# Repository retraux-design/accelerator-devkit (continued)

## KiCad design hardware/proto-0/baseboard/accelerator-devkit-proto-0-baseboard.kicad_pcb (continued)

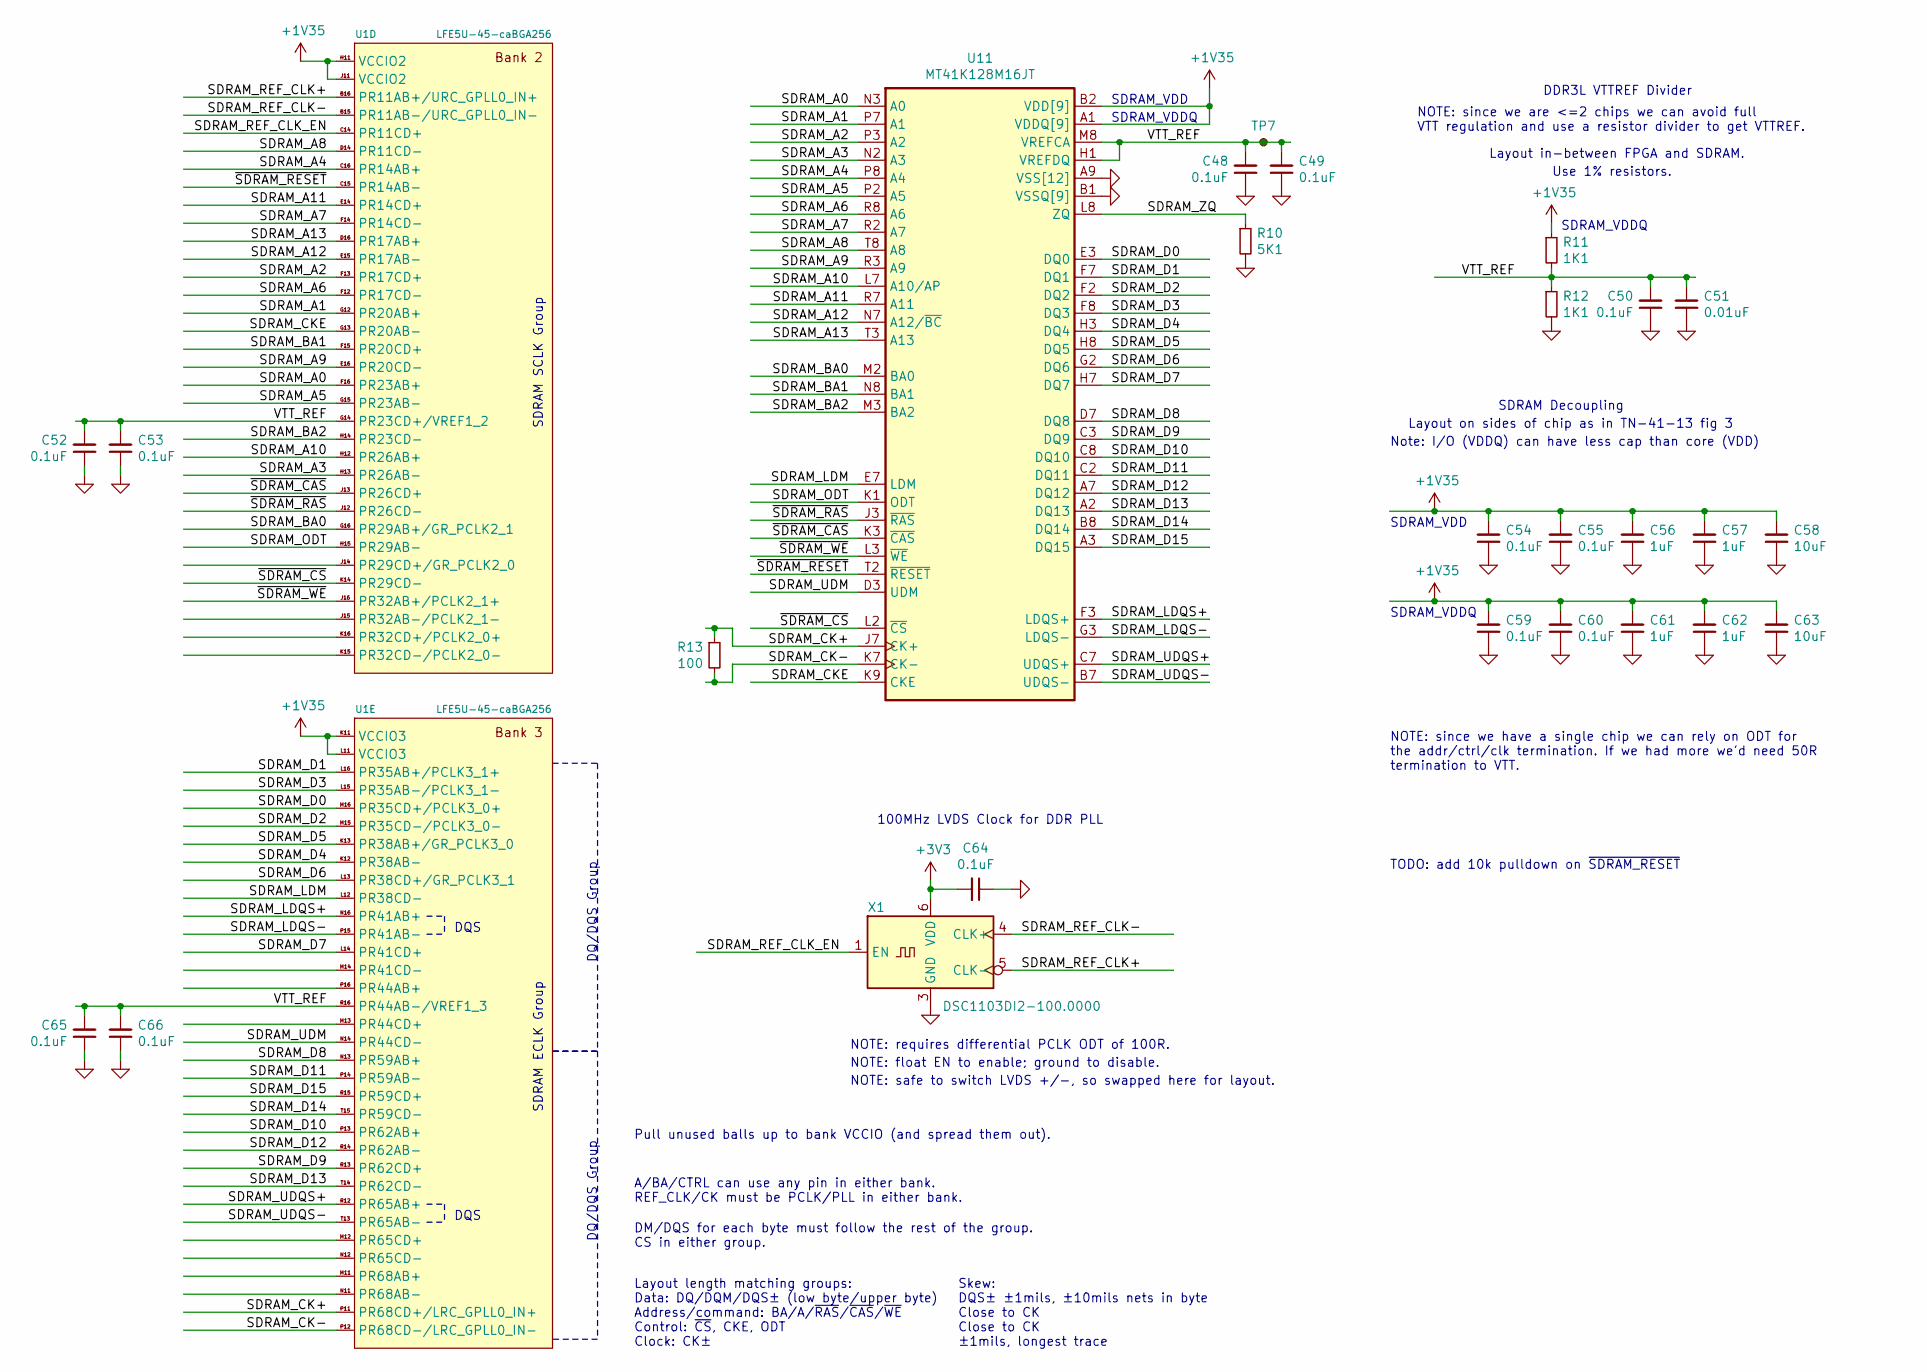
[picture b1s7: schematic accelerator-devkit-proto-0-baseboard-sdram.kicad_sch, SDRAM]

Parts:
C48, C49, C50, C52, C53, C54, C55, C59, C60, C65, C66: 0.1uF; C_0201_0603Metric
C51: 0.01uF; C_0201_0603Metric
C56, C57, C61, C62: 1uF; C_0201_0603Metric
C58, C63: 10uF; C_0402_1005Metric
C64: 0.1uF; C_0402_1005Metric
R10: 5K1; R_0402_1005Metric
R11, R12: 1K1; R_0402_1005Metric
R13: 100; R_0402_1005Metric
TP7: TestPoint_Small; TestPoint_Pad_D1.0mm
U1: LFE5U-45-caBGA256; Lattice_caBGA-256_14x14mm_P0.8mm
U11: MT41K128M16JT; BGA-96_9.0x13.0mm_Layout2x3x16_P0.8mm
X1: DSC1103DI2-100.0000; Oscillator_SMD_Microchip_VDFN-6Pin_2.5x2.0mm_J7A

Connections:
+1V35: C54.2, C55.2, C56.2, C57.2, C58.2, C59.2, C60.2, C61.2, C62.2, C63.2, R11.1, U1.H11 (VCCIO2), U1.J11 (VCCIO2), U1.K11 (VCCIO3), U1.L11 (VCCIO3), U11.A1 (VDDQ[9]), U11.A8 (VDDQ), U11.B2 (VDD[9]), U11.C1 (VDDQ), U11.C9 (VDDQ), U11.D2 (VDDQ), U11.D9 (VDD), U11.E9 (VDDQ), U11.F1 (VDDQ), U11.G7 (VDD), U11.H2 (VDDQ), U11.H9 (VDDQ), U11.K2 (VDD), U11.K8 (VDD), U11.N1 (VDD), U11.N9 (VDD), U11.R1 (VDD), U11.R9 (VDD); also elsewhere on the board
+3V3: C64.2, X1.6 (VDD); also elsewhere on the board
/SDRAM/SDRAM_A0: U1.F16 (PR23AB+), U11.N3 (A0)
/SDRAM/SDRAM_A1: U1.G12 (PR20AB+), U11.P7 (A1)
/SDRAM/SDRAM_A2: U1.F13 (PR17CD+), U11.P3 (A2)
/SDRAM/SDRAM_A3: U1.H13 (PR26AB-), U11.N2 (A3)
/SDRAM/SDRAM_A4: U1.C16 (PR14AB+), U11.P8 (A4)
/SDRAM/SDRAM_A5: U1.G15 (PR23AB-), U11.P2 (A5)
/SDRAM/SDRAM_A6: U1.F12 (PR17CD-), U11.R8 (A6)
/SDRAM/SDRAM_A7: U1.F14 (PR14CD-), U11.R2 (A7)
/SDRAM/SDRAM_A8: U1.D14 (PR11CD-), U11.T8 (A8)
/SDRAM/SDRAM_A9: U1.E16 (PR20CD-), U11.R3 (A9)
/SDRAM/SDRAM_A10: U1.H12 (PR26AB+), U11.L7 (A10/AP)
/SDRAM/SDRAM_A11: U1.E14 (PR14CD+), U11.R7 (A11)
/SDRAM/SDRAM_A12: U1.E15 (PR17AB-), U11.N7 (A12/~BC)
/SDRAM/SDRAM_A13: U1.D16 (PR17AB+), U11.T3 (A13)
/SDRAM/SDRAM_BA0: U1.G16 (PR29AB+/GR_PCLK2_1), U11.M2 (BA0)
/SDRAM/SDRAM_BA1: U1.F15 (PR20CD+), U11.N8 (BA1)
/SDRAM/SDRAM_BA2: U1.H14 (PR23CD-), U11.M3 (BA2)
/SDRAM/SDRAM_CK+: R13.1, U1.P11 (PR68CD+/LRC_GPLL0_IN+), U11.J7 (CK+)
/SDRAM/SDRAM_CK-: R13.2, U1.P12 (PR68CD-/LRC_GPLL0_IN-), U11.K7 (CK-)
/SDRAM/SDRAM_CKE: U1.G13 (PR20AB-), U11.K9 (CKE)
/SDRAM/SDRAM_D0: U1.M16 (PR35CD+/PCLK3_0+), U11.E3 (DQ0)
/SDRAM/SDRAM_D1: U1.L16 (PR35AB+/PCLK3_1+), U11.F7 (DQ1)
/SDRAM/SDRAM_D2: U1.M15 (PR35CD-/PCLK3_0-), U11.F2 (DQ2)
/SDRAM/SDRAM_D3: U1.L15 (PR35AB-/PCLK3_1-), U11.F8 (DQ3)
/SDRAM/SDRAM_D4: U1.K12 (PR38AB-), U11.H3 (DQ4)
/SDRAM/SDRAM_D5: U1.K13 (PR38AB+/GR_PCLK3_0), U11.H8 (DQ5)
/SDRAM/SDRAM_D6: U1.L13 (PR38CD+/GR_PCLK3_1), U11.G2 (DQ6)
/SDRAM/SDRAM_D7: U1.L14 (PR41CD+), U11.H7 (DQ7)
/SDRAM/SDRAM_D8: U1.N13 (PR59AB+), U11.D7 (DQ8)
/SDRAM/SDRAM_D9: U1.R13 (PR62CD+), U11.C3 (DQ9)
/SDRAM/SDRAM_D10: U1.P13 (PR62AB+), U11.C8 (DQ10)
/SDRAM/SDRAM_D11: U1.P14 (PR59AB-), U11.C2 (DQ11)
/SDRAM/SDRAM_D12: U1.R14 (PR62AB-), U11.A7 (DQ12)
/SDRAM/SDRAM_D13: U1.T14 (PR62CD-), U11.A2 (DQ13)
/SDRAM/SDRAM_D14: U1.T15 (PR59CD-), U11.B8 (DQ14)
/SDRAM/SDRAM_D15: U1.R15 (PR59CD+), U11.A3 (DQ15)
/SDRAM/SDRAM_LDM: U1.L12 (PR38CD-), U11.E7 (LDM)
/SDRAM/SDRAM_LDQS+: U1.N16 (PR41AB+), U11.F3 (LDQS+)
/SDRAM/SDRAM_LDQS-: U1.P15 (PR41AB-), U11.G3 (LDQS-)
/SDRAM/SDRAM_ODT: U1.H15 (PR29AB-), U11.K1 (ODT)
/SDRAM/SDRAM_REF_CLK+: U1.B16 (PR11AB+/URC_GPLL0_IN+), X1.5 (CLK-)
/SDRAM/SDRAM_REF_CLK-: U1.B15 (PR11AB-/URC_GPLL0_IN-), X1.4 (CLK+)
/SDRAM/SDRAM_REF_CLK_EN: U1.C14 (PR11CD+), X1.1 (EN)
/SDRAM/SDRAM_UDM: U1.N14 (PR44CD-), U11.D3 (UDM)
/SDRAM/SDRAM_UDQS+: U1.R12 (PR65AB+), U11.C7 (UDQS+)
/SDRAM/SDRAM_UDQS-: U1.T13 (PR65AB-), U11.B7 (UDQS-)
/SDRAM/SDRAM_ZQ: R10.1, U11.L8 (ZQ)
/SDRAM/VTT_REF: C48.2, C49.2, C50.2, C51.2, C52.2, C53.2, C65.2, C66.2, R11.2, R12.1, TP7.1, U1.G14 (PR23CD+/VREF1_2), U1.R16 (PR44AB-/VREF1_3), U11.H1 (VREFDQ), U11.M8 (VREFCA)
/SDRAM/~SDRAM_CAS: U1.J13 (PR26CD+), U11.K3 (~CAS)
/SDRAM/~SDRAM_CS: U1.K14 (PR29CD-), U11.L2 (~CS)
/SDRAM/~SDRAM_RAS: U1.J12 (PR26CD-), U11.J3 (~RAS)
/SDRAM/~SDRAM_RESET: U1.C15 (PR14AB-), U11.T2 (~RESET)
/SDRAM/~SDRAM_WE: U1.J16 (PR32AB+/PCLK2_1+), U11.L3 (~WE)
GND: C48.1, C49.1, C50.1, C51.1, C52.1, C53.1, C54.1, C55.1, C56.1, C57.1, C58.1, C59.1, C60.1, C61.1, C62.1, C63.1, C64.1, C65.1, C66.1, R10.2, R12.2, U11.A9 (VSS[12]), U11.B1 (VSSQ[9]), U11.B3 (VSS), U11.B9 (VSSQ), U11.D1 (VSSQ), U11.D8 (VSSQ), U11.E1 (VSS), U11.E2 (VSSQ), U11.E8 (VSSQ), U11.F9 (VSSQ), U11.G1 (VSSQ), U11.G8 (VSS), U11.G9 (VSSQ), U11.J2 (VSS), U11.J8 (VSS), U11.M1 (VSS), U11.M9 (VSS), U11.P1 (VSS), U11.P9 (VSS), U11.T1 (VSS), U11.T9 (VSS), X1.3 (GND); also elsewhere on the board

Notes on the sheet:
DQS
SDRAM SCLK Group
SDRAM ECLK Group
DQ/DQS Group
Pull unused balls up to bank VCCIO (and spread them out).
A/BA/CTRL can use any pin in either bank. REF_CLK/CK must be PCLK/PLL in either bank.
DM/DQS for each byte must follow the rest of the group. CS in either group.
Layout length matching groups: Data: DQ/DQM/DQS± (low byte/upper byte) Address/command: BA/A/~RAS~/~CAS~/~WE~ Control: ~CS~, CKE, ODT Clock: CK±
NOTE: requires differential PCLK ODT of 100R.
NOTE: float EN to enable; ground to disable.
NOTE: safe to switch LVDS +/-, so swapped here for layout.
100MHz LVDS Clock for DDR PLL
Skew: DQS± ±1mils, ±10mils nets in byte Close to CK Close to CK ±1mils, longest trace
SDRAM_VDD
SDRAM_VDDQ
Note: I/O (VDDQ) can have less cap than core (VDD)
NOTE: since we have a single chip we can rely on ODT for the addr/ctrl/clk termination. If we had more we'd need 50R termination to VTT.
TODO: add 10k pulldown on ~SDRAM_RESET
Layout on sides of chip as in TN-41-13 fig 3
NOTE: since we are <=2 chips we can avoid full VTT regulation and use a resistor divider to get VTTREF.
Layout in-between FPGA and SDRAM.
SDRAM Decoupling
DDR3L VTTREF Divider
Use 1% resistors.

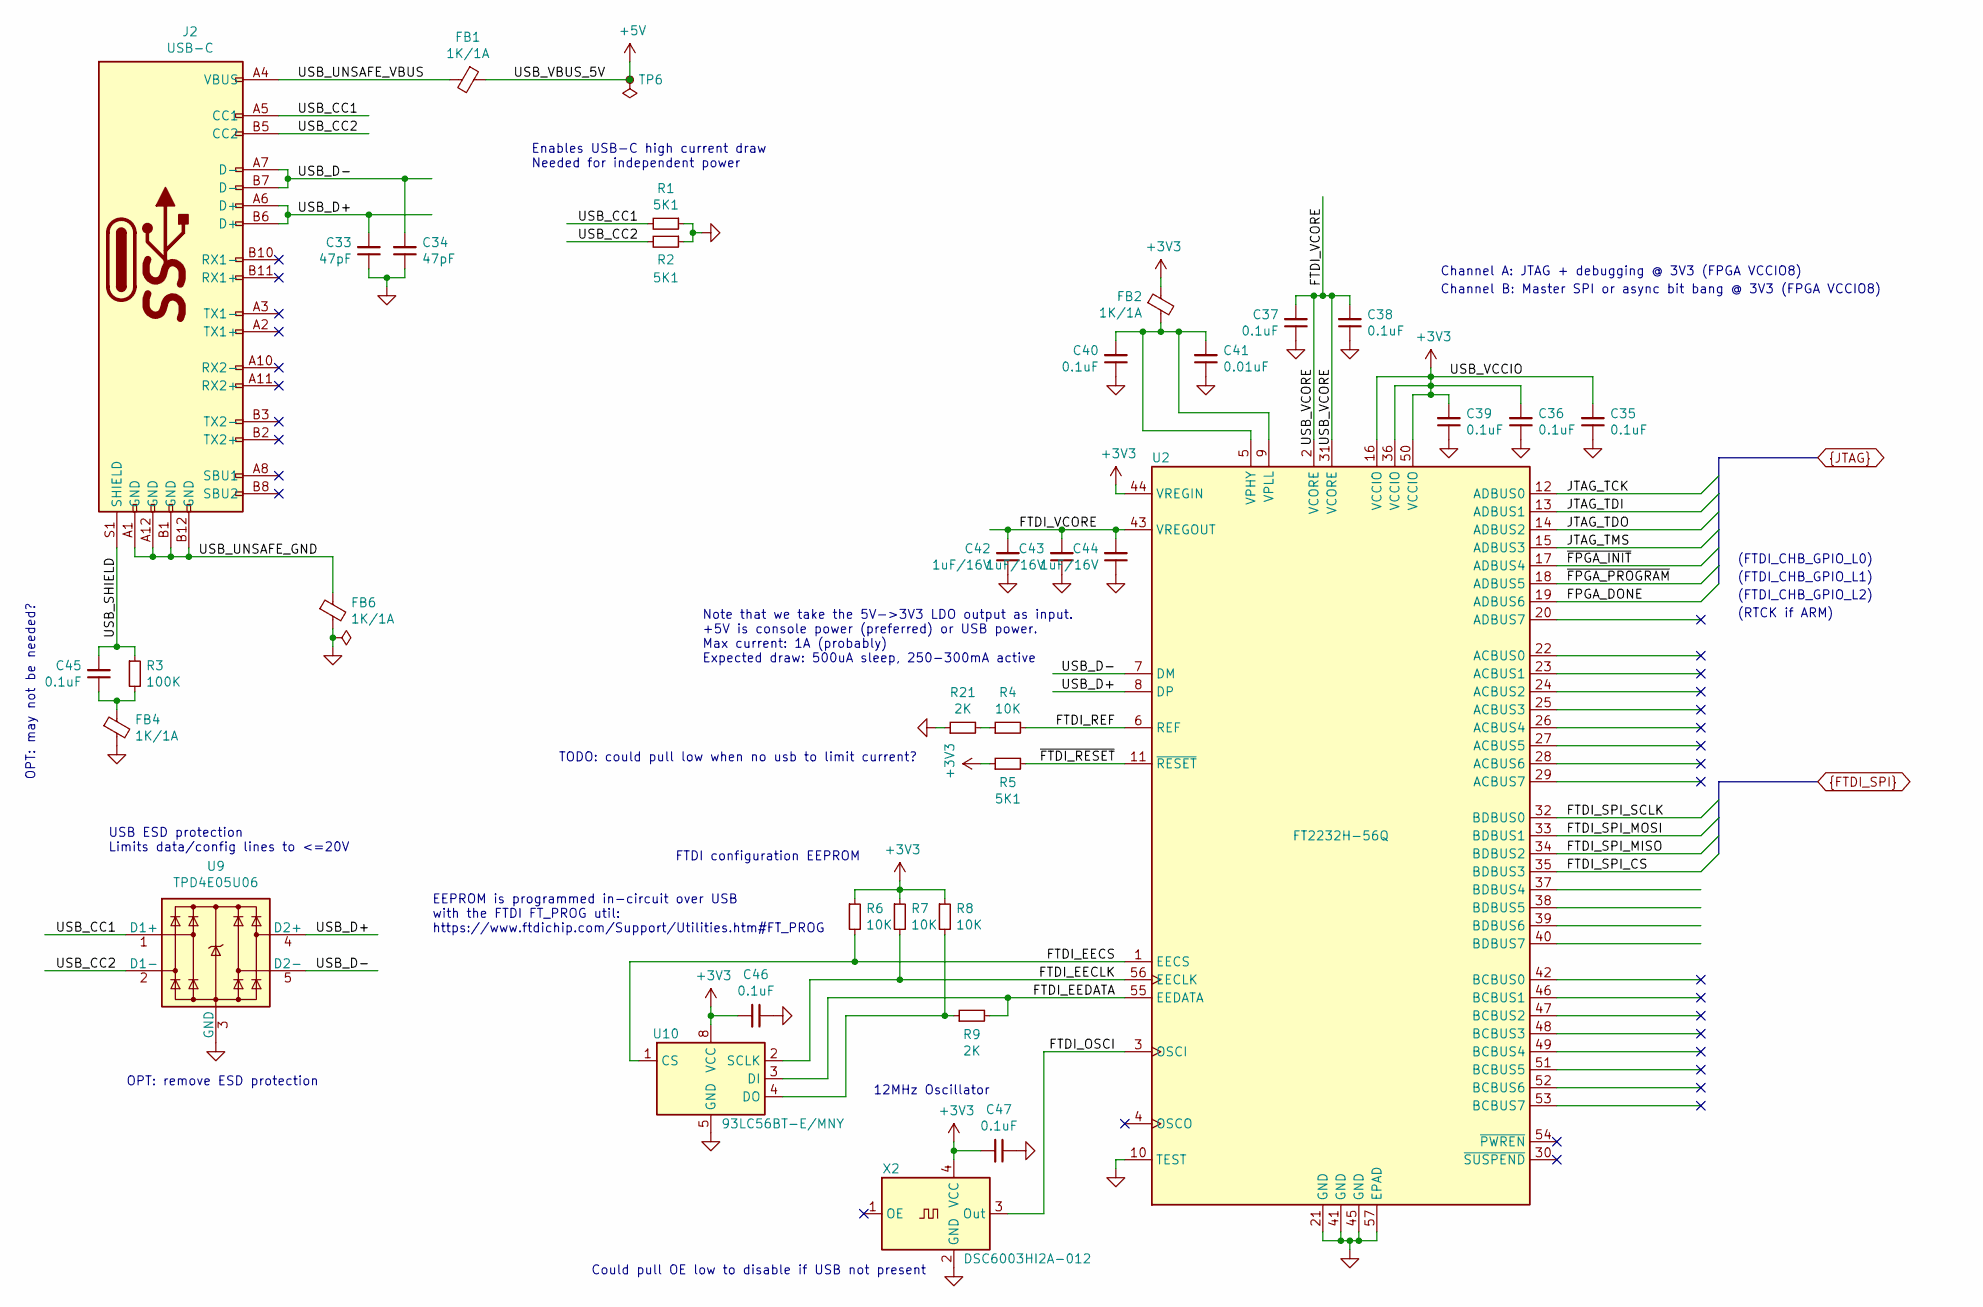
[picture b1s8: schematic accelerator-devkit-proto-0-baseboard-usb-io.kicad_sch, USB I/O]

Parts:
C33, C34: 47pF; C_0402_1005Metric
C35, C36, C37, C38, C39, C40, C45, C46, C47: 0.1uF; C_0402_1005Metric
C41: 0.01uF; C_0201_0603Metric
C42, C43, C44: 1uF/16V; C_0402_1005Metric
FB1, FB2, FB4, FB6: 1K/1A; L_0805_2012Metric; Part NFZ2MSD102SZ10L
J2: USB-C; CUI_UJ31-CH-3-MSMT-TR-67
R1, R2, R5: 5K1; R_0402_1005Metric
R3: 100K; R_0402_1005Metric
R4, R6, R7, R8: 10K; R_0402_1005Metric
R9, R21: 2K; R_0402_1005Metric
TP6: TestPoint_Small; TestPoint_THTPad_D1.0mm_Drill0.5mm
U2: FT2232H-56Q; QFN-56-1EP_8x8mm_P0.5mm_EP5.9x5.9mm_ThermalVias
U9: TPD4E05U06; USON-10_2.5x1.0mm_P0.5mm
U10: 93LC56BT-E/MNY; WDFN-8-1EP_3x2mm_P0.5mm_EP1.3x1.4mm
X2: DSC6003HI2A-012; Oscillator_SMD_Microchip_VFLGA-4Pin_1.6x1.2mm

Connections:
+3V3: C35.2, C36.2, C39.2, C46.2, C47.2, FB2.1, R5.1, R6.1, R7.1, R8.1, U2.16 (VCCIO), U2.36 (VCCIO), U2.44 (VREGIN), U2.50 (VCCIO), U10.8 (VCC), X2.4 (VCC); also elsewhere on the board
+5V: FB1.1, TP6.1; also elsewhere on the board
/USB-I/O/FTDI_EECLK: R7.2, U2.56 (EECLK), U10.2 (SCLK)
/USB-I/O/FTDI_EECS: R6.2, U2.1 (EECS), U10.1 (CS)
/USB-I/O/FTDI_EEDATA: R9.2, U2.55 (EEDATA), U10.3 (DI)
/USB-I/O/FTDI_OSCI: U2.3 (OSCI), X2.3 (Out)
/USB-I/O/FTDI_REF: R4.2, U2.6 (REF)
/USB-I/O/FTDI_VCORE: C37.2, C38.2, C42.2, C43.2, C44.2, U2.2 (VCORE), U2.31 (VCORE), U2.43 (VREGOUT)
/USB-I/O/USB_CC1: J2.A5 (CC1), R1.2, U9.1 (D1+), U9.10 (D1+)
/USB-I/O/USB_CC2: J2.B5 (CC2), R2.2, U9.2 (D1-), U9.9 (D1-)
/USB-I/O/USB_D+: C33.2, J2.A6 (D+), J2.B6 (D+), U2.8 (DP), U9.4 (D2+), U9.7 (D2+)
/USB-I/O/USB_D-: C34.2, J2.A7 (D-), J2.B7 (D-), U2.7 (DM), U9.5 (D2-), U9.6 (D2-)
/USB-I/O/USB_SHIELD: C45.2, J2.S1 (SHIELD), R3.1
/USB-I/O/USB_UNSAFE_GND: FB6.1, J2.A1 (GND), J2.A12 (GND), J2.B1 (GND), J2.B12 (GND)
/USB-I/O/USB_UNSAFE_VBUS: FB1.2, J2.A4 (VBUS), J2.A9 (VBUS), J2.B4 (VBUS), J2.B9 (VBUS)
/USB-I/O/~FTDI_RESET: R5.2, U2.11 (~RESET)
FPGA_DONE: U2.19 (ADBUS6); also elsewhere on the board
FTDI_SPI_CS: U2.35 (BDBUS3); also elsewhere on the board
FTDI_SPI_MISO: U2.34 (BDBUS2); also elsewhere on the board
FTDI_SPI_MOSI: U2.33 (BDBUS1); also elsewhere on the board
FTDI_SPI_SCLK: U2.32 (BDBUS0); also elsewhere on the board
GND: C33.1, C34.1, C35.1, C36.1, C37.1, C38.1, C39.1, C40.1, C41.1, C42.1, C43.1, C44.1, C46.1, C47.1, FB4.2, FB6.2, R1.1, R2.1, R21.1, U2.10 (TEST), U2.21 (GND), U2.41 (GND), U2.45 (GND), U2.57 (EPAD), U9.3 (GND), U9.8 (GND), U10.5 (GND), X2.2 (GND); also elsewhere on the board
JTAG_TCK: U2.12 (ADBUS0); also elsewhere on the board
JTAG_TDI: U2.13 (ADBUS1); also elsewhere on the board
JTAG_TDO: U2.14 (ADBUS2); also elsewhere on the board
JTAG_TMS: U2.15 (ADBUS3); also elsewhere on the board
unnamed: C40.2, C41.2, FB2.2, U2.5 (VPHY), U2.9 (VPLL)
unnamed: C45.1, FB4.1, R3.2
unnamed: R8.2, R9.1, U10.4 (DO)
unnamed: R4.1, R21.2
~FPGA_INIT: U2.17 (ADBUS4); also elsewhere on the board
~FPGA_PROGRAM: U2.18 (ADBUS5); also elsewhere on the board

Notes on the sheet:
OPT: may not be needed?
USB ESD protection Limits data/config lines to <=20V
OPT: remove ESD protection
EEPROM is programmed in-circuit over USB with the FTDI FT_PROG util: https://www.ftdichip.com/Support/Utilities.htm#FT_PROG
Enables USB-C high current draw Needed for independent power
FTDI configuration EEPROM
Note that we take the 5V->3V3 LDO output as input. +5V is console power (preferred) or USB power. Max current: 1A (probably) Expected draw: 500uA sleep, 250-300mA active
12MHz Oscillator
TODO: could pull low when no usb to limit current?
Could pull OE low to disable if USB not present
Channel A: JTAG + debugging @ 3V3 (FPGA VCCIO8)
Channel B: Master SPI or async bit bang @ 3V3 (FPGA VCCIO8)
(FTDI_CHB_GPIO_L0)
(FTDI_CHB_GPIO_L1)
(FTDI_CHB_GPIO_L2)
(RTCK if ARM)

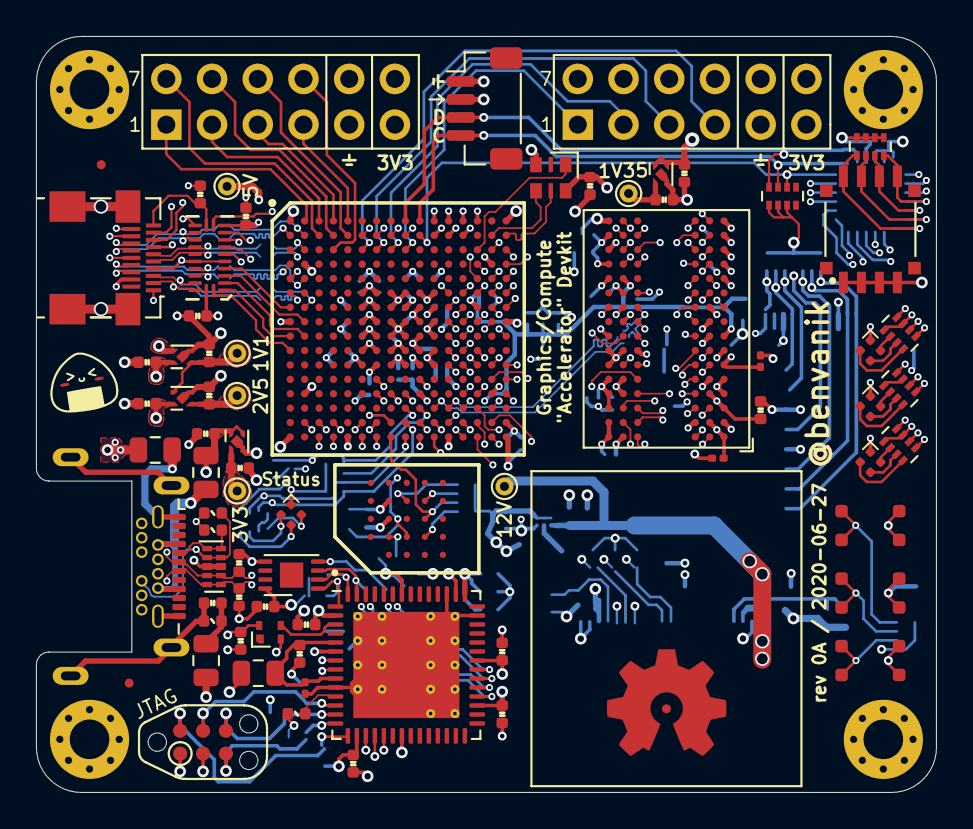
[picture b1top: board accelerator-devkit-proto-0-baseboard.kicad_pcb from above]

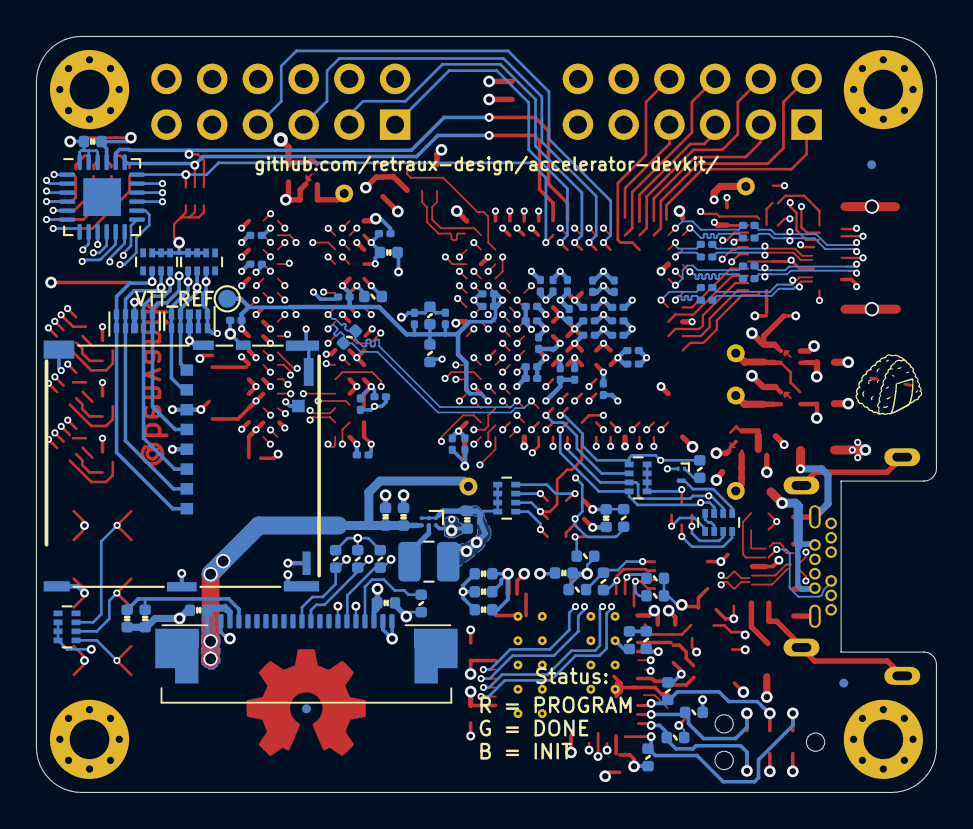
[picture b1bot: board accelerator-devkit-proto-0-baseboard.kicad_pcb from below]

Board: 6 copper layers, 50.0 x 42.0 mm, 174 parts (95 on the bottom side), 192 nets.

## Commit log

2020-06-26 Initial revision 0
    Untested!
2020-06-26 Removing unused MP Pin on Qwiic connector
2020-06-26 Adding logo connections between schematic and PCB.
2020-06-26 Adding TODO for adding more GND stitch vias near DDR
2020-06-26 Adding silkscreen annotations to Qwiic connector
2020-06-26 Adding additional silkscreen info
2020-06-26 Fixing Qwiic courtyard
2020-06-26 Fixing 1V35 silkscreen label size
2020-06-26 Fixing silkscreen text sizes
2020-06-26 Adding some ground stitch vias
2020-06-26 Thickening sDRAM_VREF traces
2020-06-26 Length matching SDRAM upper byte
2020-06-27 Length matching SDRAM lower byte
2020-06-27 Length matching SDRAM In3.Cu nets
2020-06-27 Cleaning up messy overlapping traces
2020-06-27 Retuning lengths after cleanup
2020-06-27 Removing TODO now that lengths are matched
2020-06-27 Removing top/bottom ground pours
2020-06-27 Spreading out display SDIO nets
2020-06-27 Moving all power rail test points to the front
2020-06-27 Bumping board datestamp
2020-06-27 Removing VTT_REF roundabout
2020-06-27 Moving traces in from the board edge
2020-06-27 Onigiri <3
2020-06-28 Switching USB connector to CUI UJ31-CH-3-MSMT-TR-67
2020-06-28 Adding fiducials and marking as rev 0A
